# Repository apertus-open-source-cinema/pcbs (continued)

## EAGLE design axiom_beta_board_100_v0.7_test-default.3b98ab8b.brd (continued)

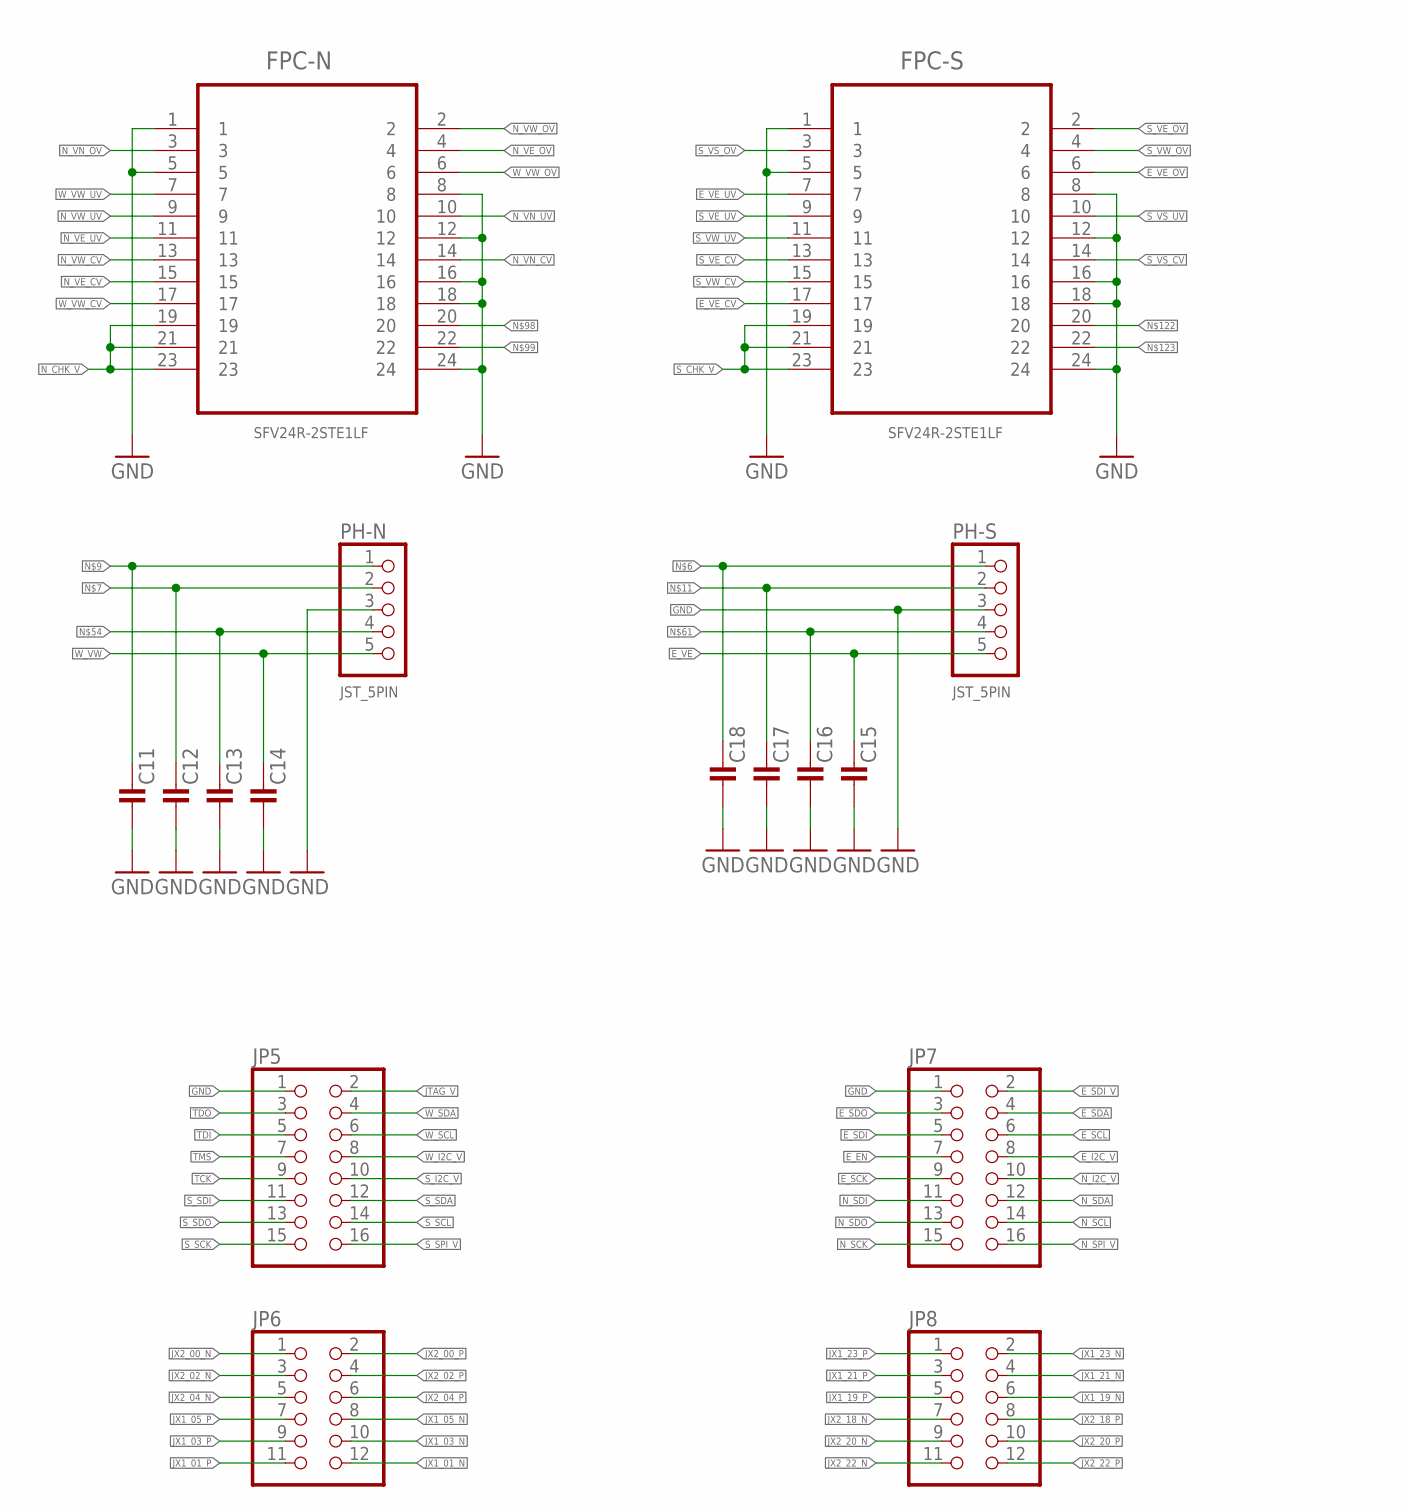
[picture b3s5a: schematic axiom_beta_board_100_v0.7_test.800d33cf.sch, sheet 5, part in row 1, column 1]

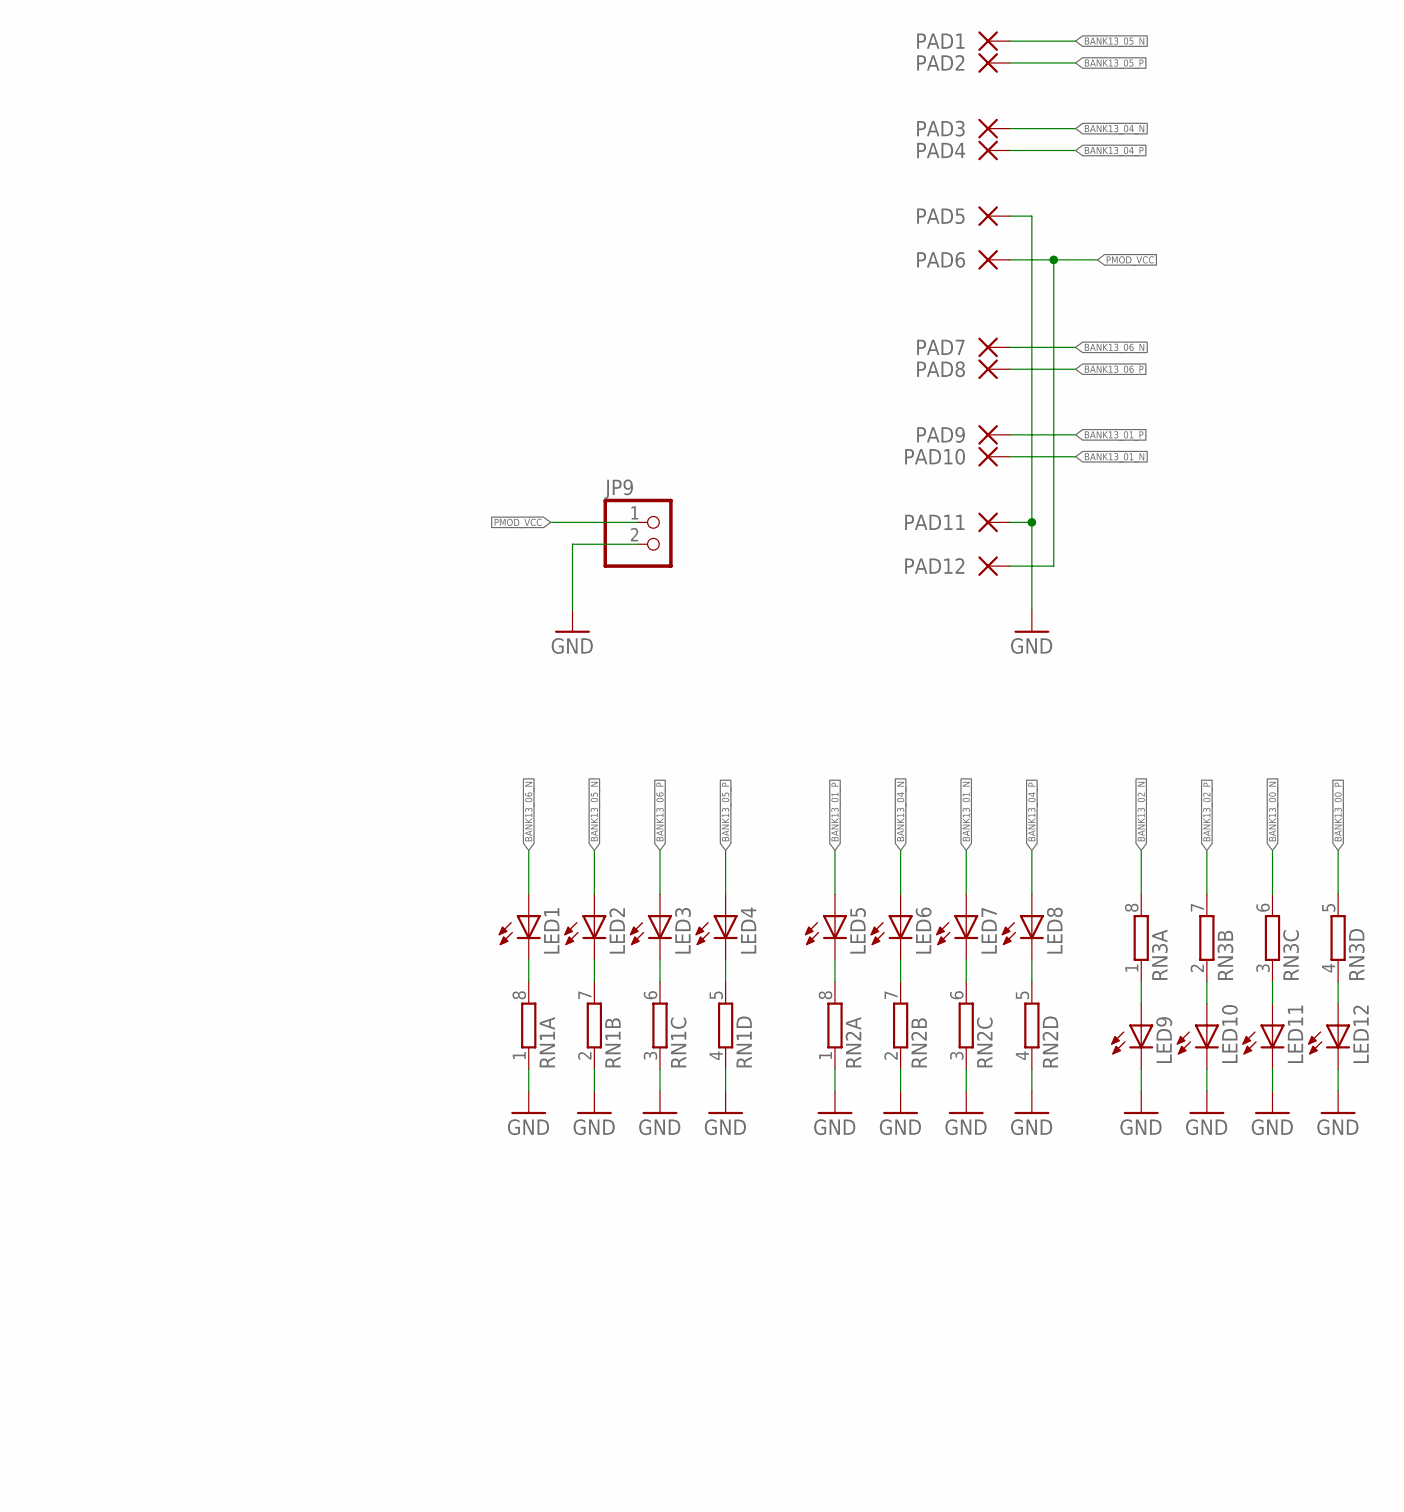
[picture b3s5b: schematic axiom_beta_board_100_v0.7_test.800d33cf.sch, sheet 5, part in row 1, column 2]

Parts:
C11, C12, C13, C14, C15, C16, C17, C18: C1206-B; 1206-B
FPC-N: SFV24R-2STE1LF; FCI_SFV24R-2STE1LF
FPC-S: SFV24R-2STE1LF; FCI_SFV24R-2STE1LF
JP5, JP7: PINHD-2X08_2.54; 2X08
JP6, JP8: PINHD-2X06_2.54; 2X06
JP9: PINHD-1X02_2.54; 1X02
LED1, LED2, LED3, LED4, LED5, LED6, LED7, LED8, LED9, LED10, LED11, LED12: LEDCHIPLED_0603; CHIPLED_0603
PAD1, PAD2, PAD3, PAD4, PAD5, PAD6, PAD7, PAD8, PAD9, PAD10, PAD11, PAD12: SMD-PAD1.6X3.8MM-U; 1.6X3.8U-MM
PH-N: JST_5PIN; JST-PH-5-SMT-RA
PH-S: JST_5PIN; JST-PH-5-SMT-RA
RN1, RN2, RN3: 4R-NCAY16; CAY16

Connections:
BANK13_00_N: RN3.6 (2); also elsewhere on the board
BANK13_00_P: RN3.5 (2); also elsewhere on the board
BANK13_01_N: LED7.A, PAD10.1; also elsewhere on the board
BANK13_01_P: LED5.A, PAD9.1; also elsewhere on the board
BANK13_02_N: RN3.8 (2); also elsewhere on the board
BANK13_02_P: RN3.7 (2); also elsewhere on the board
BANK13_04_N: LED6.A, PAD3.1; also elsewhere on the board
BANK13_04_P: LED8.A, PAD4.1; also elsewhere on the board
BANK13_05_N: LED2.A, PAD1.1; also elsewhere on the board
BANK13_05_P: LED4.A, PAD2.1; also elsewhere on the board
BANK13_06_N: LED1.A, PAD7.1; also elsewhere on the board
BANK13_06_P: LED3.A, PAD8.1; also elsewhere on the board
E_EN: JP7.7; also elsewhere on the board
E_I2C_V: JP7.8; also elsewhere on the board
E_SCK: JP7.9; also elsewhere on the board
E_SCL: JP7.6; also elsewhere on the board
E_SDA: JP7.4; also elsewhere on the board
E_SDI: JP7.5; also elsewhere on the board
E_SDI_V: JP7.2; also elsewhere on the board
E_SDO: JP7.3; also elsewhere on the board
E_VE: C15.1, PH-S.5; also elsewhere on the board
E_VE_CV: FPC-S.17; also elsewhere on the board
E_VE_OV: FPC-S.6; also elsewhere on the board
E_VE_UV: FPC-S.7; also elsewhere on the board
JTAG_V: JP5.2; also elsewhere on the board
JX1_01_N: JP6.12; also elsewhere on the board
JX1_01_P: JP6.11; also elsewhere on the board
JX1_03_N: JP6.10; also elsewhere on the board
JX1_03_P: JP6.9; also elsewhere on the board
JX1_05_N: JP6.8; also elsewhere on the board
JX1_05_P: JP6.7; also elsewhere on the board
JX1_19_N: JP8.6; also elsewhere on the board
JX1_19_P: JP8.5; also elsewhere on the board
JX1_21_N: JP8.4; also elsewhere on the board
JX1_21_P: JP8.3; also elsewhere on the board
JX1_23_N: JP8.2; also elsewhere on the board
JX1_23_P: JP8.1; also elsewhere on the board
JX2_00_N: JP6.1; also elsewhere on the board
JX2_00_P: JP6.2; also elsewhere on the board
JX2_02_N: JP6.3; also elsewhere on the board
JX2_02_P: JP6.4; also elsewhere on the board
JX2_04_N: JP6.5; also elsewhere on the board
JX2_04_P: JP6.6; also elsewhere on the board
JX2_18_N: JP8.7; also elsewhere on the board
JX2_18_P: JP8.8; also elsewhere on the board
JX2_20_N: JP8.9; also elsewhere on the board
JX2_20_P: JP8.10; also elsewhere on the board
JX2_22_N: JP8.11; also elsewhere on the board
JX2_22_P: JP8.12; also elsewhere on the board
unnamed: LED1.C, RN1.8 (2)
unnamed: LED2.C, RN1.7 (2)
unnamed: LED3.C, RN1.6 (2)
unnamed: LED4.C, RN1.5 (2)
unnamed: LED5.C, RN2.8 (2)
unnamed: LED6.C, RN2.7 (2)
unnamed: LED7.C, RN2.6 (2)
unnamed: LED8.C, RN2.5 (2)
unnamed: LED9.A, RN3.1
unnamed: LED10.A, RN3.2 (1)
unnamed: LED11.A, RN3.3 (1)
unnamed: LED12.A, RN3.4 (1)
N_CHK_V: FPC-N.19, FPC-N.21, FPC-N.23; also elsewhere on the board
N_I2C_V: JP7.10; also elsewhere on the board
N_SCK: JP7.15; also elsewhere on the board
N_SCL: JP7.14; also elsewhere on the board
N_SDA: JP7.12; also elsewhere on the board
N_SDI: JP7.11; also elsewhere on the board
N_SDO: JP7.13; also elsewhere on the board
N_SPI_V: JP7.16; also elsewhere on the board
N_VE_CV: FPC-N.15; also elsewhere on the board
N_VE_OV: FPC-N.4; also elsewhere on the board
N_VE_UV: FPC-N.11; also elsewhere on the board
N_VN_CV: FPC-N.14; also elsewhere on the board
N_VN_OV: FPC-N.3; also elsewhere on the board
N_VN_UV: FPC-N.10; also elsewhere on the board
N_VW_CV: FPC-N.13; also elsewhere on the board
N_VW_OV: FPC-N.2; also elsewhere on the board
N_VW_UV: FPC-N.9; also elsewhere on the board
PMOD_VCC: JP9.1, PAD6.1, PAD12.1
S_CHK_V: FPC-S.19, FPC-S.21, FPC-S.23; also elsewhere on the board
S_I2C_V: JP5.10; also elsewhere on the board
S_SCK: JP5.15; also elsewhere on the board
S_SCL: JP5.14; also elsewhere on the board
S_SDA: JP5.12; also elsewhere on the board
S_SDI: JP5.11; also elsewhere on the board
S_SDO: JP5.13; also elsewhere on the board
S_SPI_V: JP5.16; also elsewhere on the board
S_VE_CV: FPC-S.13; also elsewhere on the board
S_VE_OV: FPC-S.2; also elsewhere on the board
S_VE_UV: FPC-S.9; also elsewhere on the board
S_VS_CV: FPC-S.14; also elsewhere on the board
S_VS_OV: FPC-S.3; also elsewhere on the board
S_VS_UV: FPC-S.10; also elsewhere on the board
S_VW_CV: FPC-S.15; also elsewhere on the board
S_VW_OV: FPC-S.4; also elsewhere on the board
S_VW_UV: FPC-S.11; also elsewhere on the board
TCK: JP5.9; also elsewhere on the board
TDI: JP5.5; also elsewhere on the board
TDO: JP5.3; also elsewhere on the board
TMS: JP5.7; also elsewhere on the board
W_I2C_V: JP5.8; also elsewhere on the board
W_SCL: JP5.6; also elsewhere on the board
W_SDA: JP5.4; also elsewhere on the board
W_VW: C14.1, PH-N.5; also elsewhere on the board
W_VW_CV: FPC-N.17; also elsewhere on the board
W_VW_OV: FPC-N.6; also elsewhere on the board
W_VW_UV: FPC-N.7; also elsewhere on the board

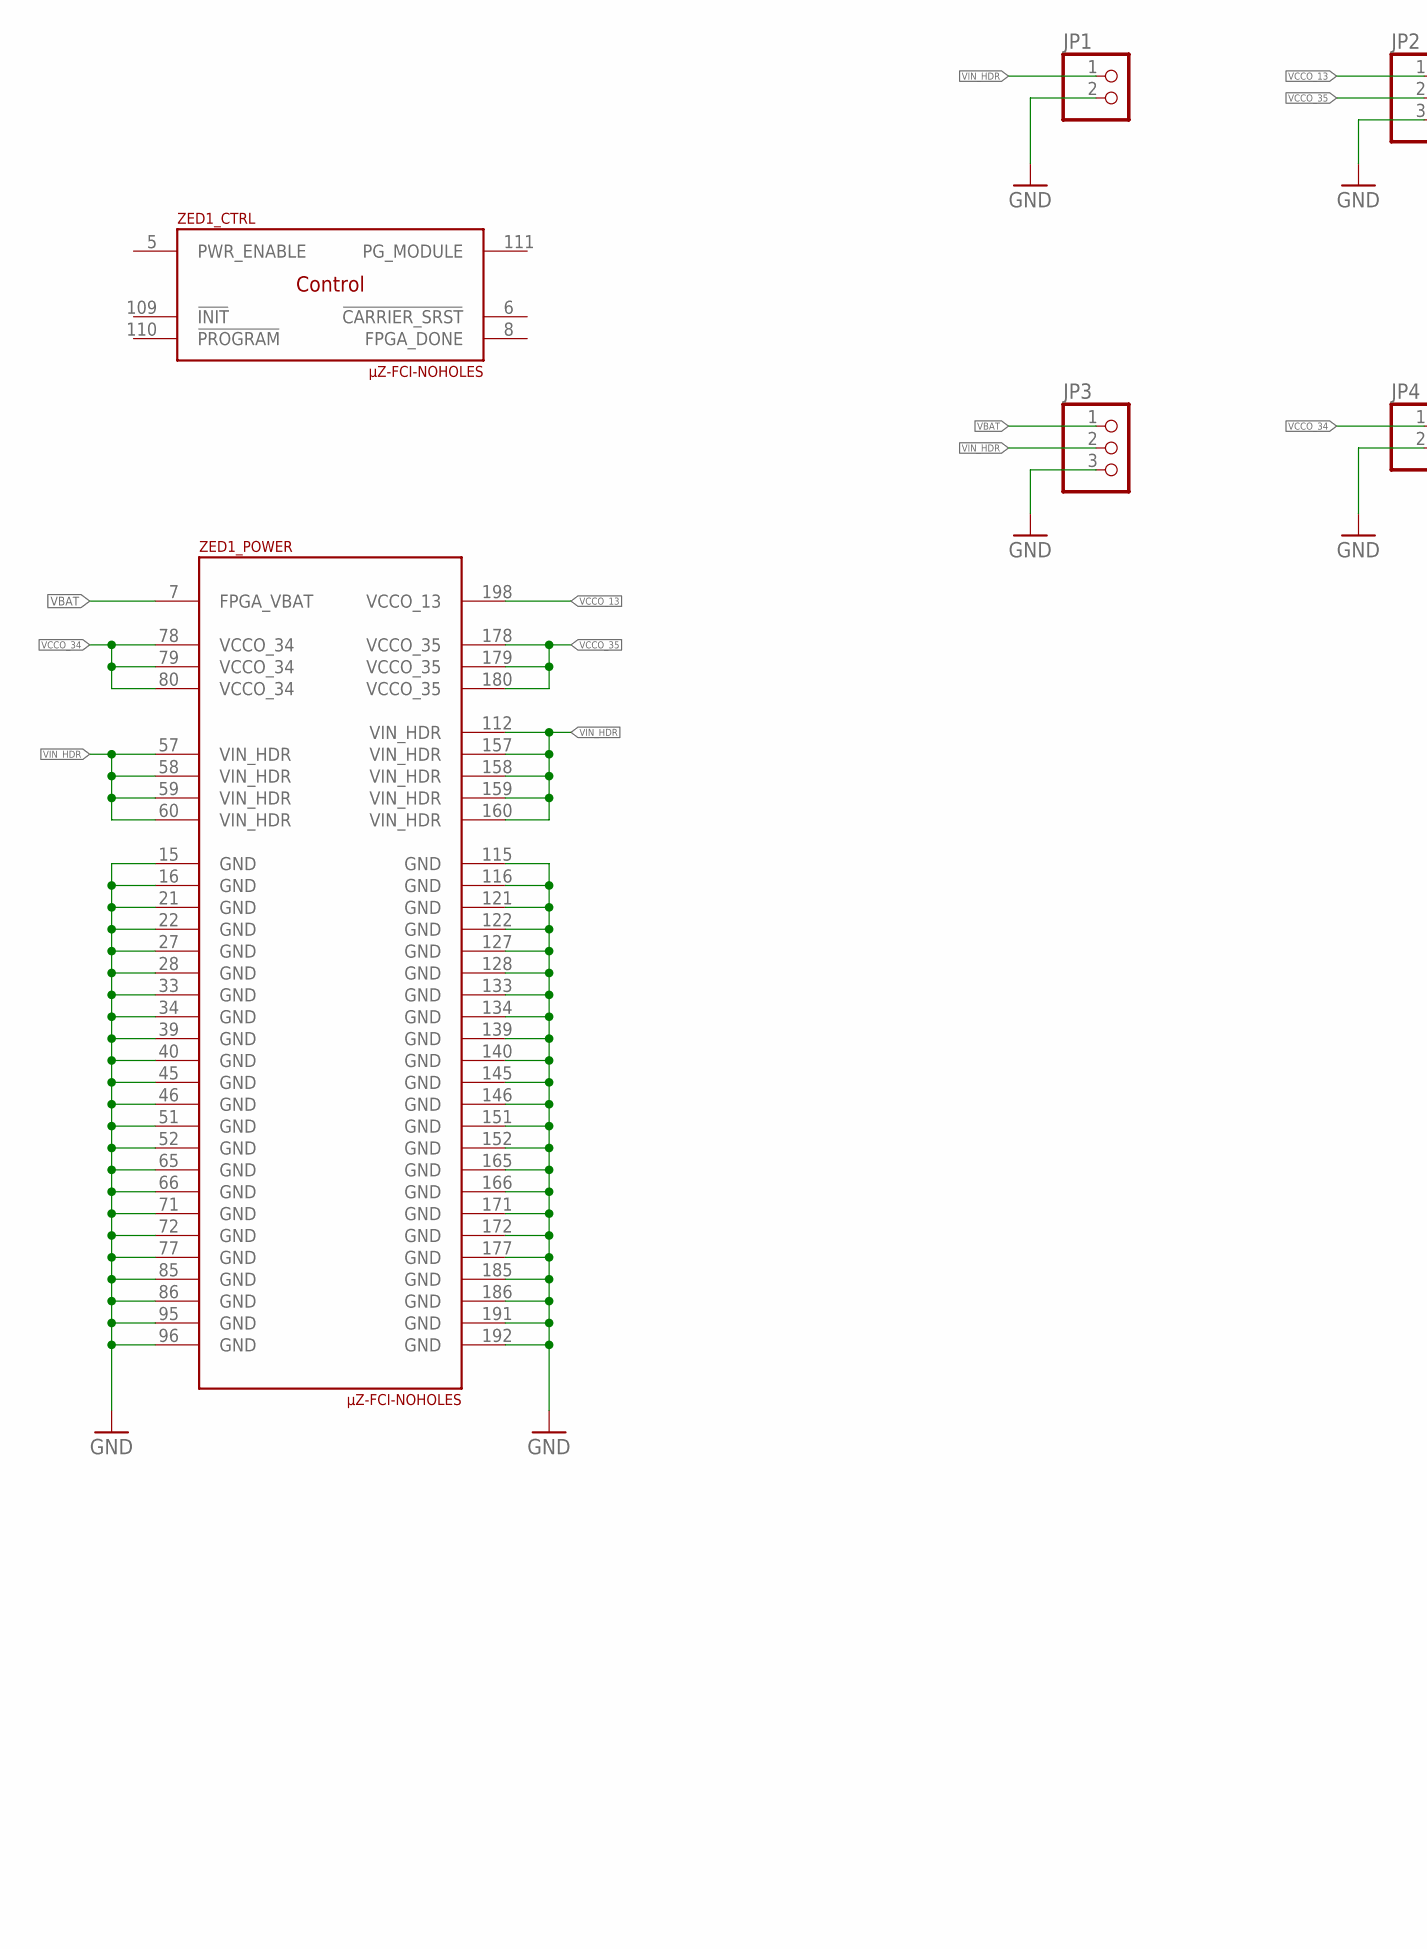
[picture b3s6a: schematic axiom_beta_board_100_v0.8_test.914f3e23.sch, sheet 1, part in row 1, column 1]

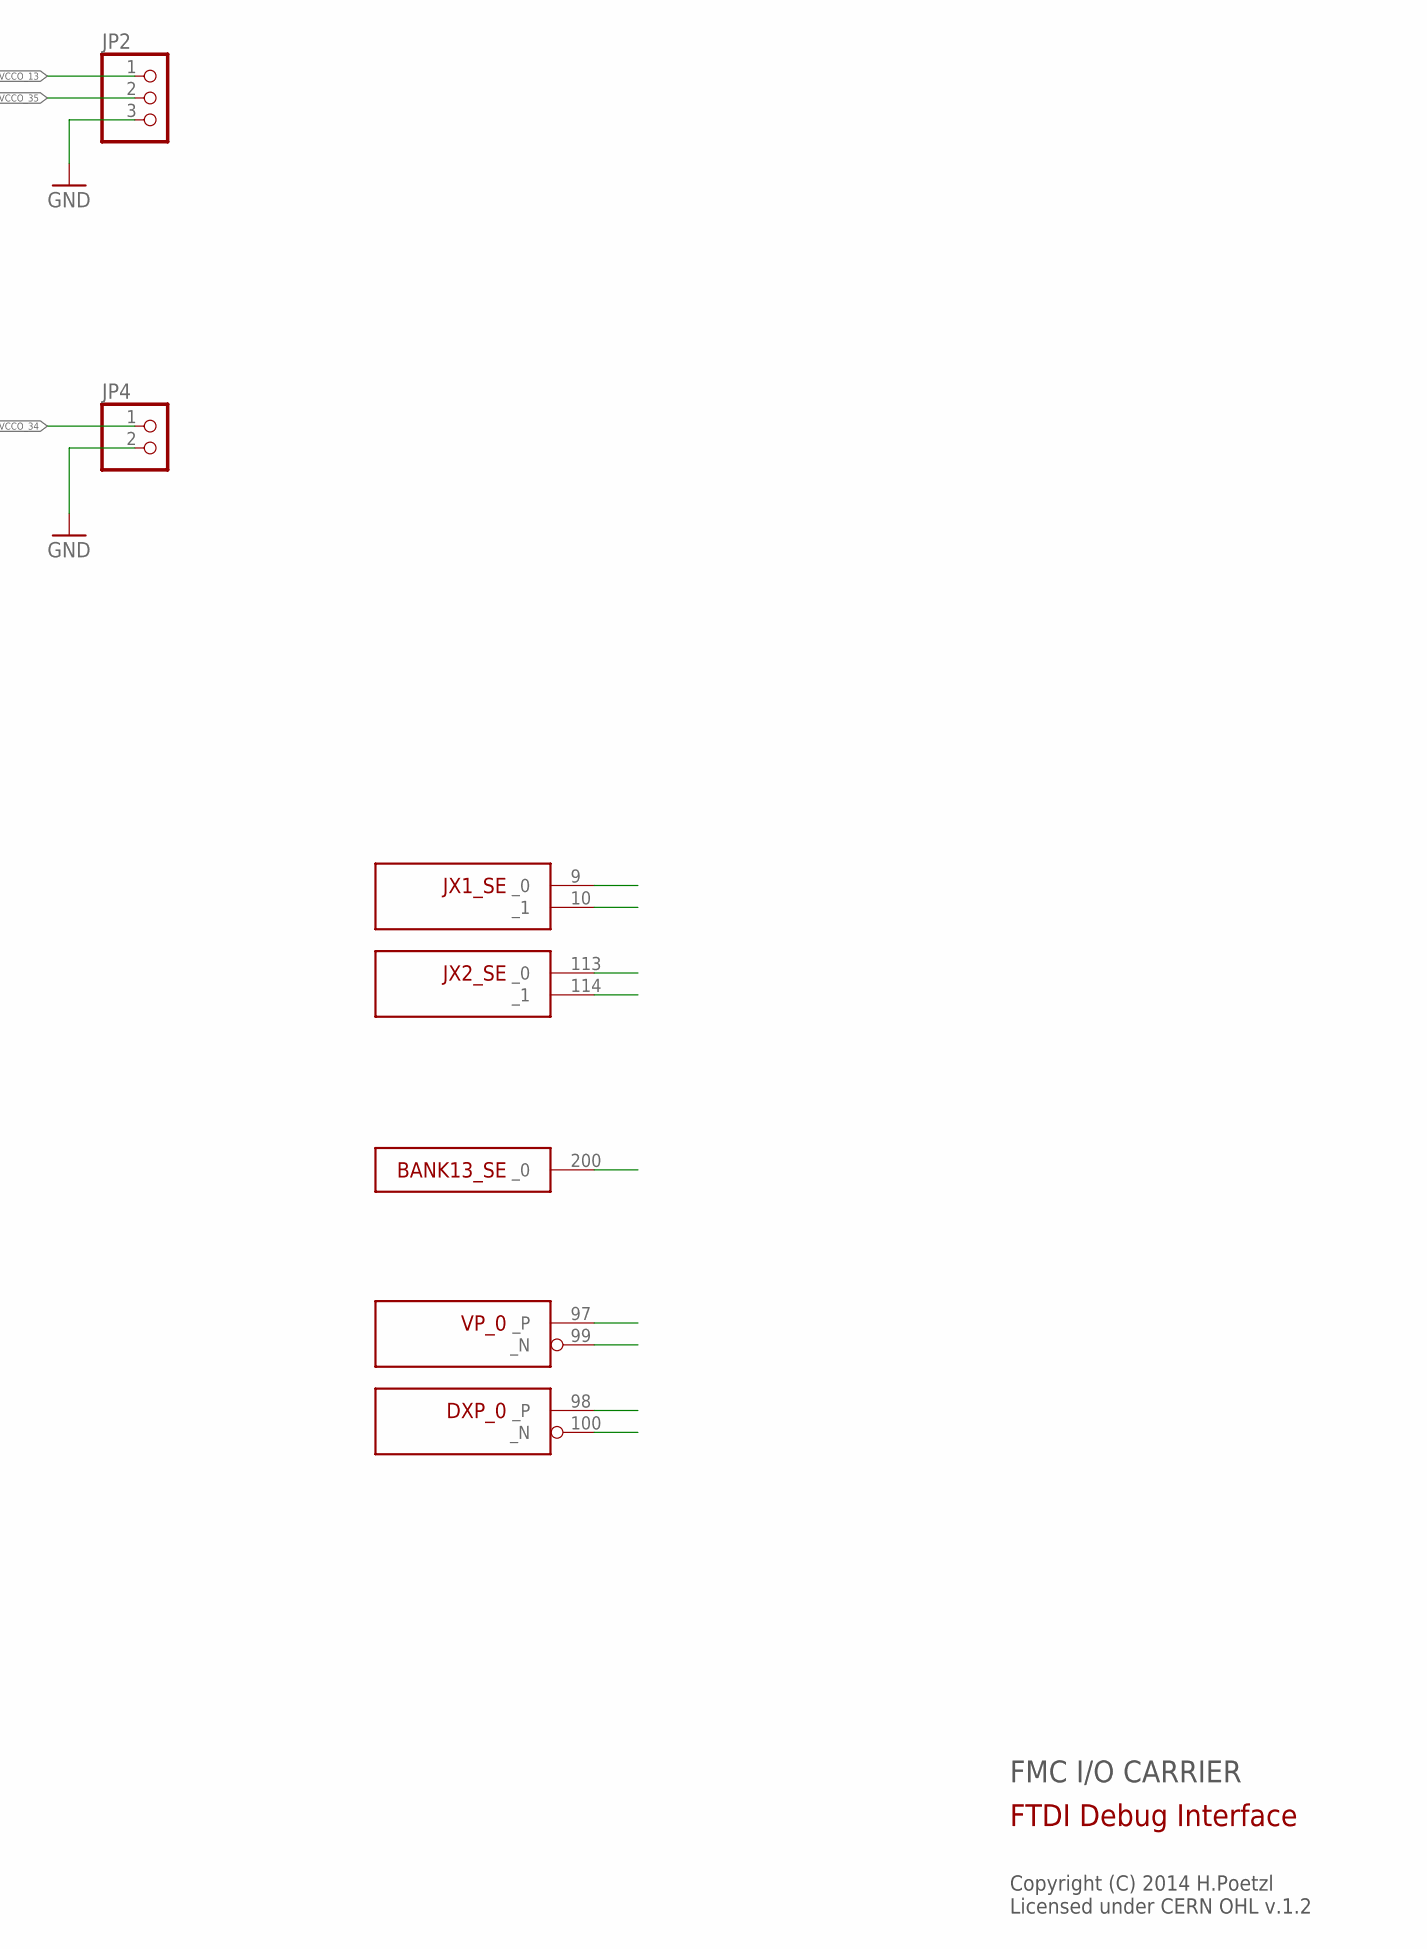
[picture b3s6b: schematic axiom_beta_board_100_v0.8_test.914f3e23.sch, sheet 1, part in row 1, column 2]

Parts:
JP1, JP4: PINHD-1X02_2.54; 1X02
JP2, JP3: PINHD-1X03_2.54; 1X03
ZED1: µZ-FCI-NOHOLES; µZ-NOHOLES

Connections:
VBAT: JP3.1, ZED1.7 (FPGA_VBAT)
VCCO_13: JP2.1, ZED1.198 (VCCO_13)
VCCO_34: JP4.1, ZED1.78 (VCCO_34), ZED1.79 (VCCO_34), ZED1.80 (VCCO_34)
VCCO_35: JP2.2, ZED1.178 (VCCO_35), ZED1.179 (VCCO_35), ZED1.180 (VCCO_35)
VIN_HDR: JP1.1, JP3.2, ZED1.57 (VIN_HDR), ZED1.58 (VIN_HDR), ZED1.59 (VIN_HDR), ZED1.60 (VIN_HDR), ZED1.112 (VIN_HDR), ZED1.157 (VIN_HDR), ZED1.158 (VIN_HDR), ZED1.159 (VIN_HDR), ZED1.160 (VIN_HDR)

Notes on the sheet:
FMC I/O CARRIER
Copyright (C) 2014 H.Poetzl Licensed under CERN OHL v.1.2
FTDI Debug Interface

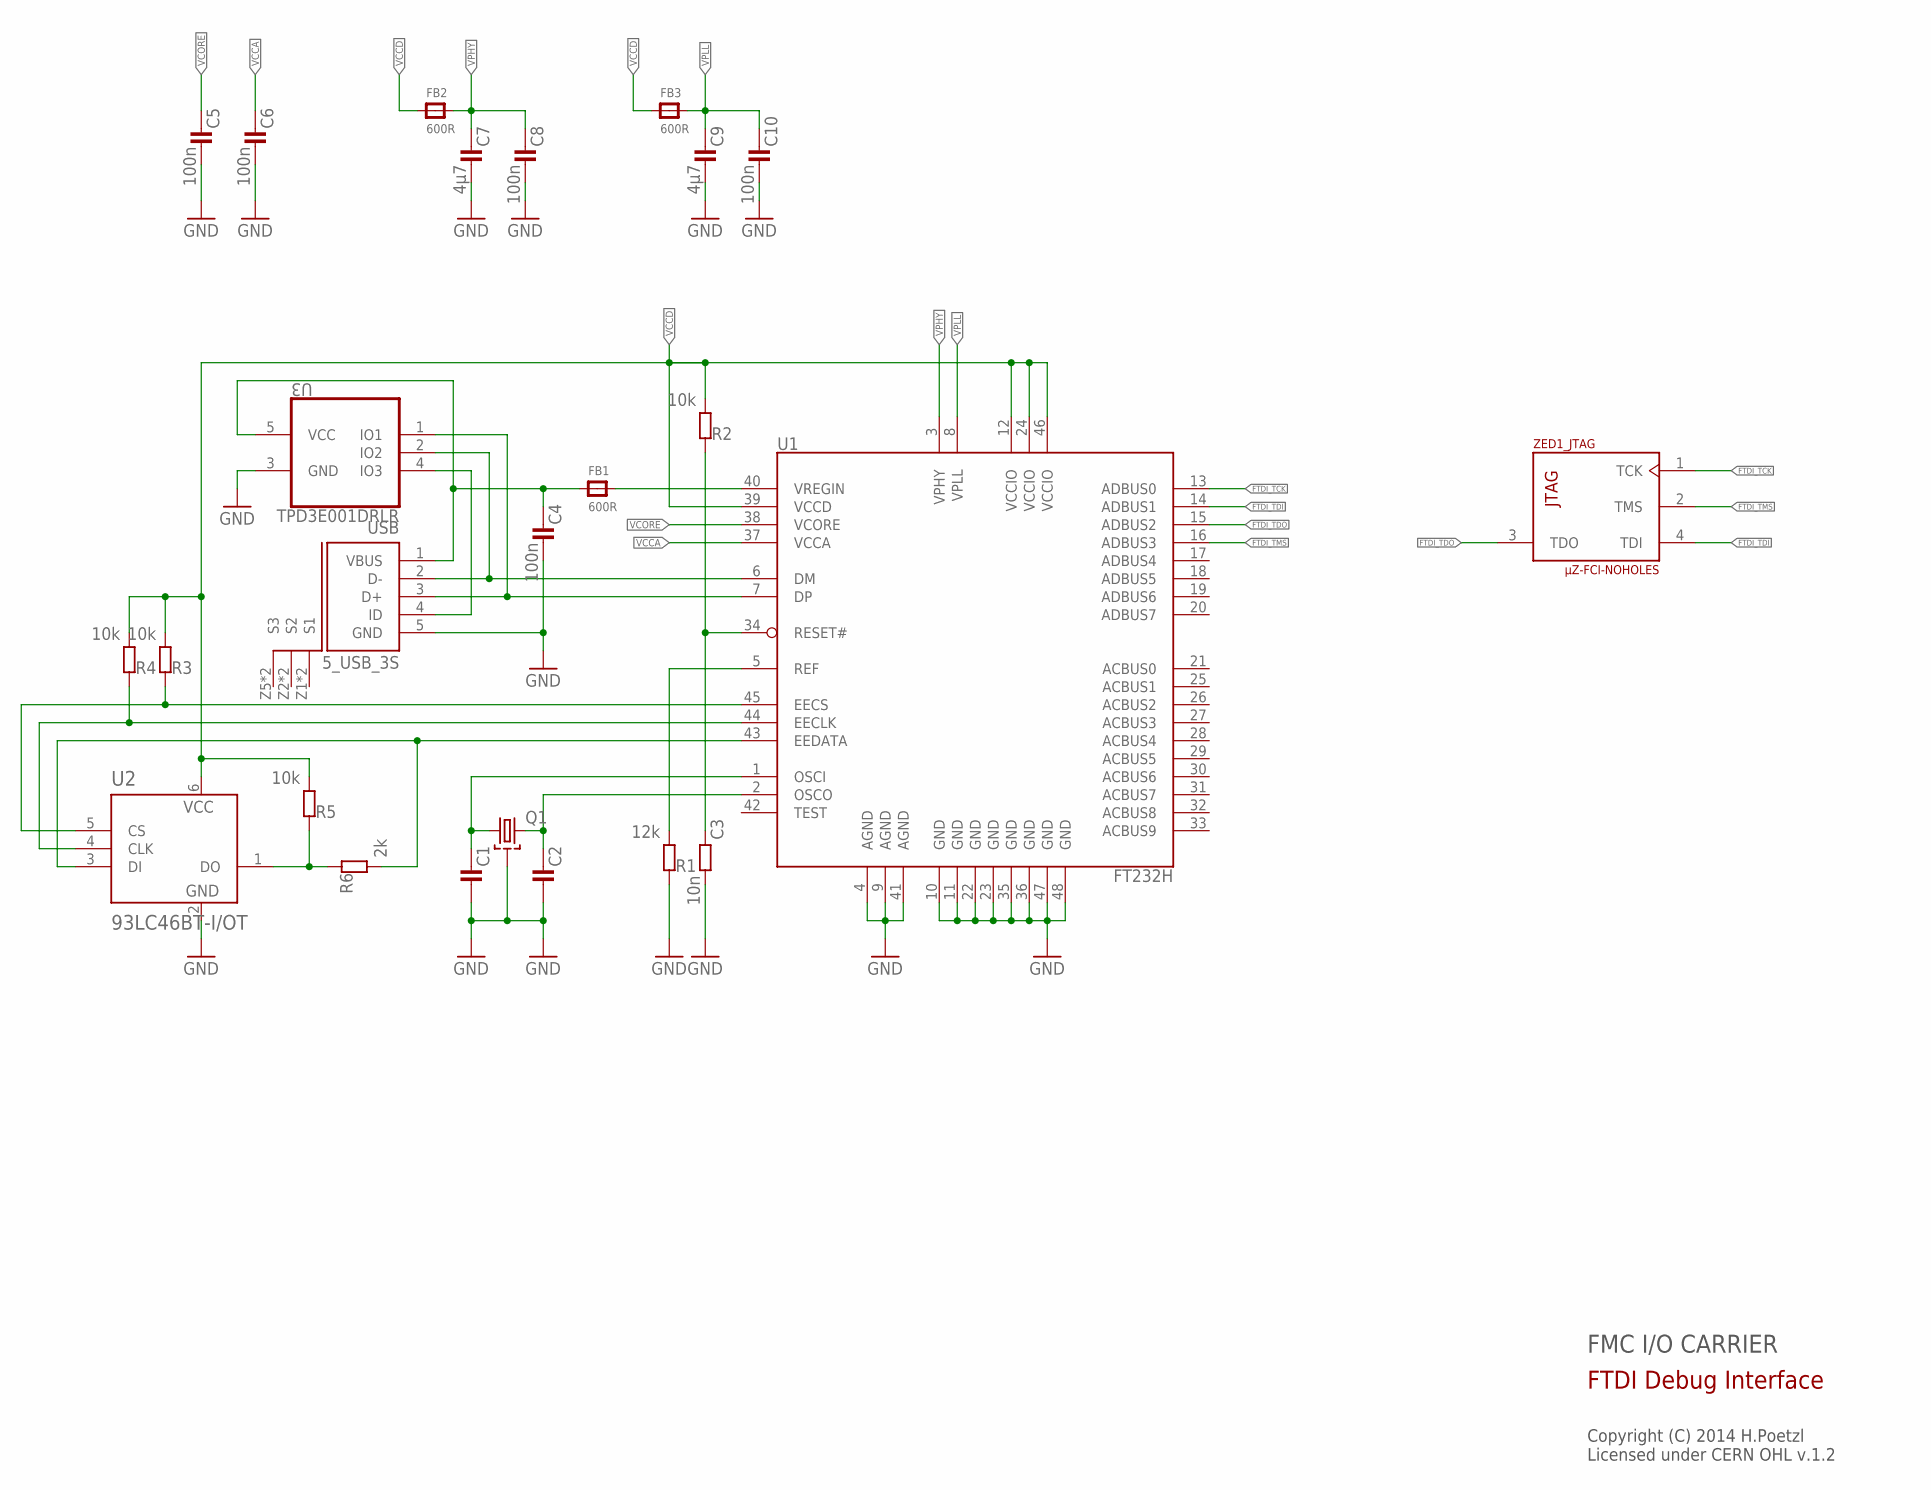
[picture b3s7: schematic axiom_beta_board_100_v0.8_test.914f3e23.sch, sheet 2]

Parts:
C1, C2: C0402-B; 0402-B
C3: 10n; 0402-B
C4: 100n; 0603-B
C5, C6, C8, C10: 100n; 0402-B
C7, C9: 4µ7; 0603-B
FB1, FB2, FB3: 600R; _0603MP
Q1: SMD-4P-2G-3.2X2.5; ABM8G
R1: 12k; 0402-B
R2, R3, R4, R5: 10k; 0402-B
R6: 2k; 0402-B
U1: FT232H; LQFP48
U2: 93LC46BT-I/OT; SOT95P280X145-6N
U3: TPD3E001DRLR; SOT50P160X60-5N
USB: 5_USB_3S; MICRO-AB-H-SMT
ZED1: µZ-FCI-NOHOLES; µZ-NOHOLES

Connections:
EE_CLK1: R4.1, U1.44 (EECLK), U2.4 (CLK)
EE_CS1: R3.1, U1.45 (EECS), U2.5 (CS)
EE_DATA1: R6.2, U1.43 (EEDATA), U2.3 (DI)
FTDI_D_N: U1.6 (DM), U3.2 (IO2), USB.2 (D-)
FTDI_D_P: U1.7 (DP), U3.1 (IO1), USB.3 (D+)
FTDI_TCK: U1.13 (ADBUS0), ZED1.1 (TCK)
FTDI_TDI: U1.14 (ADBUS1), ZED1.4 (TDI)
FTDI_TDO: U1.15 (ADBUS2), ZED1.3 (TDO)
FTDI_TMS: U1.16 (ADBUS3), ZED1.2 (TMS)
unnamed: R5.1, R6.1, U2.1 (DO)
unnamed: C1.1, Q1.1, U1.1 (OSCI)
unnamed: C2.1, Q1.3 (2), U1.2 (OSCO)
unnamed: C3.1, R2.1, U1.34 (RESET#)
unnamed: R1.2, U1.5 (REF)
unnamed: U3.4 (IO3), USB.4 (ID)
VBUS: C4.1, FB1.1, U3.5 (VCC), USB.1 (VBUS)
VCCA: C6.1, U1.37 (VCCA)
VCCD: FB2.1, FB3.1, R2.2, R3.2, R4.2, R5.2, U1.12 (VCCIO), U1.24 (VCCIO), U1.39 (VCCD), U1.46 (VCCIO), U2.6 (VCC)
VCORE: C5.1, U1.38 (VCORE)
VPHY: C7.1, C8.1, FB2.2, U1.3 (VPHY)
VPLL: C9.1, C10.1, FB3.2, U1.8 (VPLL)
VREGIN: FB1.2, U1.40 (VREGIN)

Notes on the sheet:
FMC I/O CARRIER
Copyright (C) 2014 H.Poetzl Licensed under CERN OHL v.1.2
FTDI Debug Interface
